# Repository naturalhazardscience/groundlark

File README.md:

# Groundlark — open hardware for seismic and environmental monitoring

Groundlark is a family of hardware boards and companion software for seismic
and environmental monitoring. Each board has its own hardware directory, with
shared component libraries, interfaces and validation tools.

The family has **three products**: the Groundlark FPGA HAT, Skylark and
Burrowlark USB sensor heads. All share the sensor contracts, simulation tools and local workbench.

## Groundlark

**Seismic monitoring on a Raspberry Pi.** The active
[Groundlark FPGA HAT](hw/groundlark-fpga-hat/README.md), model **DAQHAT-01**, is a
140 × 56 mm, six-layer FR-4 board with three XYZ LSM6DSO IMUs and an ADS122C04
input for an external Racotech geophone, plus a fitted SDP32-125PA infrasound sensor and u-blox MAX-M10S GNSS with a side-facing SMA antenna connector. The stack is **Pi → HAT → Trenz
Artix-7 200T FPGA**. Pi acquisition works independently of a configured FPGA.

The [internal FPGA link](docs/fpga-host-link.md) provides six QSPI wires, UART,
reset and switched Pi-driven JTAG. An SPI echo bitstream is implemented;
accelerated sensor processing and native quad transfers remain future work.
The FPGA uses a separate Nexys Video-compatible 12 V, center-positive adapter through J83 and an onboard 3.326 V converter. See the [power limits](docs/trenz-hat.md).

**Status:** active prototype. Physical power, fit, timing, noise and thermal
qualification remain pending. See the [stack assembly guide](docs/stack-assembly.md),
[JLCPCB instructions](docs/jlcpcb-assembly.md) and [bench procedure](docs/bench-procedure.md).
The JLCPCB package targets one assembled HAT; sourcing, placement and J1 fit
checks remain open. Fabrication packages stay local in ignored `hw/releases/`.

*R3 [prototype enclosure](hw/mechanical/daqhat-01-case/README.md), current
140 mm HAT CAD with GNSS/SMA, infrasound, TI Pi supervision and independent FPGA power, vendor Trenz components and a detailed
[Pi 4B model](hw/shared/models/raspberrypi4/README.md) by integrated-circuit / FreeCAD
community (CC BY 3.0). Clear PETG appearance, risers, geophone and wiring are approximate.
Physical fit remains unqualified. [Render provenance](docs/images/groundlark-gnss.json).*

[Closed enclosure render provenance](docs/images/groundlark-gnss-closed.json).
Measured gain/offset workflows and PCB probe access are in the
[calibration guide](docs/calibration.md). Seismic recordings support local
[miniSEED export](docs/miniseed.md).

## Skylark

**Outdoor air-quality monitoring over USB.** [Skylark USB](hw/skylark-usb/README.md)
combines a vertical **90 × 100 mm PCB** with a removable sensor tray and a
**130 × 94 × 185 mm bell enclosure**.

- **Particles:** Plantower PMS5003, with separate downward-facing inlet and exhaust paths.
- **Gases:** socketed SGX-7SO2-AQ-20 sulfur dioxide and SGX-7H2S-AQ-25 hydrogen sulfide cells.
- **Weather:** SHT40 temperature/humidity and BMP390 barometric pressure.
- **Connection:** USB-C power and data through an STM32F072 microcontroller.
- **Housing:** printable bell, rear M4 keyhole mounts and a removable tray with
  separate PMS cradle and splash cover. Bottom ventilation is sheltered by a 25 mm skirt.

[Prototype firmware](sw/skylark/README.md) implements sensor acquisition and
USB streaming. The shared workbench includes Skylark simulation, recording/replay,
board-specific tests and an interactive 3D PCB. Gas data retains separate raw
working and auxiliary electrode counts; concentrations require calibration.

**Status:** Rev A PCB, Rev G enclosure and prototype firmware are implemented.
Physical fit, USB power behavior, analog performance, gas response and weather
resistance still require qualification. The ventilated enclosure has no assigned
IP rating. Follow the [PCB guide](hw/skylark-usb/README.md) and
[enclosure assembly instructions](hw/skylark-usb/mechanical/bell/README.md).

*Render: native PCB artwork and authored component models in the CAD-derived
tray, with the bell set beside it. Component bodies are dimension envelopes;
fasteners and cable dressing are illustrative. [Render provenance](docs/images/skylark-assembly.json).*

## Burrowlark

**Remote magnetic and enclosure-climate sensing over USB.**
[Burrowlark USB](hw/burrowlark-usb/README.md), model **DAQUSB-01**, carries four
RM3100 magnetometers on a 30 mm square grid and an SHT45 temperature/humidity
sensor. One STM32F042K6 coordinates their measurements and sends each sensor's
raw data and timing evidence to the Pi over USB-C.
The SDP32-125PA infrasound sensor is fitted on Groundlark DAQHAT-01.

**Status:** routed prototype hardware, MCU firmware and workbench simulation are
implemented. Physical USB, synchronization, magnetic cross-talk and noise
qualification remain pending. See the
[USB sensor-head guide](docs/usb-sensor-head.md) for interfaces and assembly details.

*Render: native 96 × 70 mm PCB with favicon, Burrowlark name and DAQUSB-01 / REV B1
silkscreen, four RM3100 modules and SHT45 U6/C10; the former infrasound
footprint and bypass capacitor are removed. Module, fuse and SHT45 bodies are simplified
dimensional envelopes. [Render provenance](hw/burrowlark-usb/boards/groundlark-field-head/render-provenance.json).*

## Sensor workbench

The dark-mode Python UI lets you switch between Groundlark, Skylark and
Burrowlark, with interactive 3D views, raw-data charts, stimulus/fault controls,
board-specific tests and recording/replay.
No hardware or Docker is required. Follow the
[beginner walkthrough](docs/sensor-workbench.md) to create your first signal.

```powershell
# Windows: set up once, then launch
./setup-ui.ps1 -Check
./ui.ps1
```

On Linux/macOS, use `sh ./setup-ui.sh --check`, then `sh ./ui.sh`.
Open **http://127.0.0.1:8080**. Tools and dependencies stay in ignored `.local/`.

This is an actual browser screenshot with simulated data. Select the geophone
can or its HAT input to highlight both and inspect the same ADC stream.
Use the **Board** selector for the FPGA HAT, Burrowlark or Skylark.
**Test selected board** runs the selected board’s checks; the HAT test covers all
six sensors over eight simulated seconds. IMU, ADC and GNSS use production Pi
drivers on modeled buses; infrasound uses a raw-response model pending its Pi
driver. Signal checks and recordings/results are downloadable.
The Groundlark GNSS panel also models disconnected or shorted antennas, lock
loss and recovery, and PPS loss independently.
The UI simulates and replays; physical acquisition uses the [Pi software](docs/sensor-software.md).
Live seismic capture stores raw geophone and IMU counts locally as
[miniSEED 3](docs/miniseed.md), with SSREC companions for diagnostics and replay.

## Project files and tests

| Directory | Contents |
| --- | --- |
| [hw/](hw/README.md) | Four product directories, shared component resources, hardware checks and SPICE. |
| [sw/](sw/README.md) | Pi acquisition, contracts, simulator, FPGA and remote firmware interfaces. |
| [docs/](docs/README.md) | Setup, hardware specifications, assembly, interfaces and testing instructions. |
| [environment/](docs/portable-lab.md) | Pinned Docker test environment and bounded cleanup tooling. |

For the full test environment, run `./lab.ps1 build` once, then `./lab.ps1 test`.
Use `./lab.ps1 test -Profile software` for sensor contracts, acquisition,
recording/replay and recovery. Use `./lab.ps1 test -Profile simulation` for fresh
circuit builds, CAD checks and all models while excluding the procurement release
gate. See the [simulation scope](docs/simulation-validation.md) and [portable lab guide](docs/portable-lab.md)
for Linux commands, test scope, five-run retention and cleanup.

Hardware sources: [DAQHAT-01 circuit](hw/groundlark-fpga-hat/elec/hat_trenz.ato),
[KiCad PCB](hw/groundlark-fpga-hat/boards/groundlark-daqhat-01/groundlark-daqhat-01.kicad_pcb),
[Burrowlark DAQUSB-01](hw/burrowlark-usb/boards/groundlark-field-head/groundlark-field-head.kicad_pcb), and
[Skylark USB](hw/skylark-usb/boards/skylark-usb/skylark-usb.kicad_pcb).
See [build instructions](docs/build.md) and [source references](docs/sources.md).

## License

Project-authored code, hardware designs and documentation use the [MIT License](LICENSE).
Third-party assets and dependencies retain their own licenses and attribution.

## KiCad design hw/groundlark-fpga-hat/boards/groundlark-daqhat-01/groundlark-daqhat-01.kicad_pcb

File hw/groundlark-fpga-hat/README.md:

# Groundlark FPGA HAT — DAQHAT-01

Underside TP90–TP93 provide passive calibration probe access; see the [bench calibration guide](../../docs/calibration.md). No additional GPIO or enclosure opening is required.

The active 140 × 56 mm, six-layer Trenz carrier combines three XYZ IMUs and
an ADS122C04 input for an external Racotech geophone, plus a fitted SDP32-125PA
infrasound pressure sensor on I2C1 (0x21), with a 200 Hz averaged acquisition
profile targeting the [1–20 Hz landslide research band](../../docs/sensor-response.md).
The stack is Raspberry Pi,
DAQHAT-01, then Trenz TE0712-03-81I36-A. Physical qualification remains pending.
J90 uses a horizontal Phoenix 1803280 header with the existing 1803581 cable
plug. Pin order remains positive, negative, shield.

MAX-M10S GNSS uses Pi I²C1 and BCM24 PPS, with a side-facing SMA and a
TPS2553 antenna fault limiter. ISO1640 side 2 faces the Pi/GNSS bus. J130 feeds
the separate MSPM0L1106 supervisor and 5.115 V Pi supply; battery policy and
physical qualification remain pending; prototype MCU firmware is implemented.
See [GNSS setup](../../docs/gnss-hardware.md) for the matched RF input and
[external pressure filter](../mechanical/daqhat-01-pressure/README.md) for the
simulation-defined pneumatic accessory; it is outside the PCB package.

J83 takes a Nexys Video-compatible 12 V, center-positive 5.5/2.1 mm adapter
rated at least 3 A. It faces the opposite edge from the geophone. U80 supplies
the FPGA independently of the Pi, with a 3 A output allocation; SW80 turns this
supply off/on. The first 25 mm of the extension contains FPGA input protection and conversion. Check the documented voltage, thermal and enclosure limits before
building; the supply remains an unqualified prototype.

- [Electrical source](elec/hat_trenz.ato)
- [Placement inputs](layout/placement.json)
- [Routed KiCad project](boards/groundlark-daqhat-01/groundlark-daqhat-01.kicad_pro)
- [Native routing snapshot](boards/groundlark-daqhat-01/groundlark-daqhat-01.ses)
- [Hardware and power specifications](../../docs/trenz-hat.md)
- [Pi and external source budgets](../../docs/power-supplies.md)
- [Sensor bandwidth and timing](../../docs/sensor-response.md)
- [Assembly instructions](../../docs/stack-assembly.md)

Build target: `trenz_hat` in [hw/ato.yaml](../ato.yaml). Use the root portable lab
for validation. `simulation/` contains bounded supporting-circuit models;
`mechanical/` retains earlier mechanical artifacts with their recorded status.
FPGA sources remain under [sw/fpga/](../../sw/fpga/README.md).

Assembly uses an 8.5 mm JLCPCB socket, two external GPIO risers and measured
supports (28.06 mm nominal Pi gap). Sensor supply and bias returns have local
ground stitches. Only the two RF inductor stock observations were refreshed on 2026-10-20; see [JLCPCB assembly](../../docs/jlcpcb-assembly.md).

D90 uses TI **TPD2E2U06QDCKRQ1 / JLCPCB C915089** as the pin-compatible
replacement for TPD2E2U06DCKR. Its SC-70 footprint and routing are unchanged.
The 190 fitted placements have 72 exact-MPN BOM lines, all with catalog
mappings. L140/L141 use Murata LQW15AN56NG80D / C1330587 and
LQW15AN3N6G80D / C412276 as documented assembly substitutions. The RF model
uses these selected parts; the sensor-acquisition/UI simulator is unchanged.
U23 uses the redesigned SDP32-125PA circuit and driver. All 190 placements now
have frozen supplier-pad registrations, including bottom-side projections,
switch mounting lands and the SMA body direction. D140 uses the manufacturer's
SOD882 land and paste dimensions. See the assembly guide before ordering.

The revised signal routing passes the expanded adjacent-layer coupling model: all
217 evaluated pairs meet the 0.20 V allocation; worst excursion is 0.188 V.
The full build enforces the supplier-placement release gate.
L141 is a provisional 3.6 nH VNA tuning position; D130 junction-temperature
qualification remains open. See [simulation scope](../../docs/simulation-validation.md).

Use the [R3 enclosure](../mechanical/daqhat-01-case/README.md) for the 140 × 56 mm
board. It adds power-wing supports, a rear DC opening opposite the geophone and
switch access. First-print fit and thermal qualification remain pending.

## Pi power supervisor

J130 accepts **8–18 V DC** from an externally protected battery/controller.
U130 is TI MSPM0L1106TRHBR; U131 powers it continuously while U132/U133 supply
and disconnect the Pi through header pins 2/4. The combined Pi/HAT allocation
is 3 A at nominal 5.115 V, for the Pi 4 stack. Do not simultaneously power the
Pi through USB-C. Keep J83's separate 12 V FPGA input independent.

Battery thresholds and delays are configurable placeholders, shipped disabled
in [power-policy.example.json](../../sw/pi/deploy/power-policy.example.json).
Prototype MCU firmware is implemented; physical power qualification remains pending. An
unprogrammed MCU leaves the Pi off; fitting the JP130 shunt provides manual
bench operation. Remove it before automatic supervision. See the
[operating specification](../../docs/power-supplies.md#pi-supervisor-and-battery-input).

## GNSS timing

U21 is a MAX-M10S-00B on Pi I2C1 (0x42); BCM24/header 18 captures PPS.
J140 is a side-facing SMA for a 3.3 V active antenna drawing at most 20 mA.
The 140 x 56 mm outline and independent FPGA power remain unchanged. Use the
updated R3 enclosure with its +X antenna access slot. See [antenna setup](../../docs/gnss-hardware.md)
and [timing capture/correlation](../../docs/utc-timing.md). Browser tests cover
modeled lock/PPS loss and recording/replay; physical millisecond alignment remains unqualified.

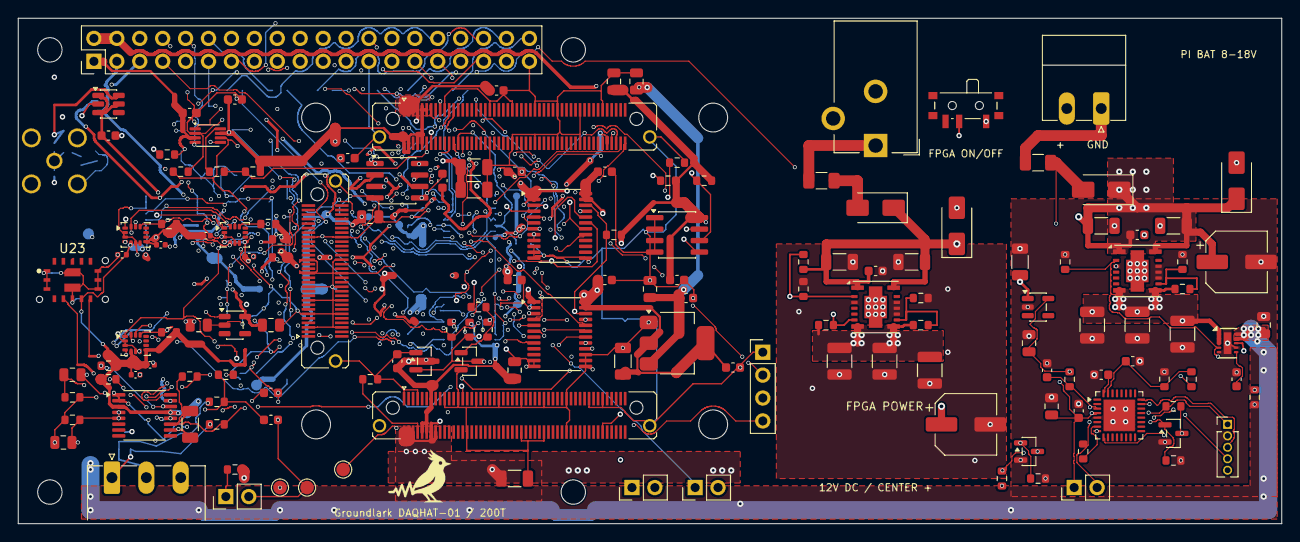
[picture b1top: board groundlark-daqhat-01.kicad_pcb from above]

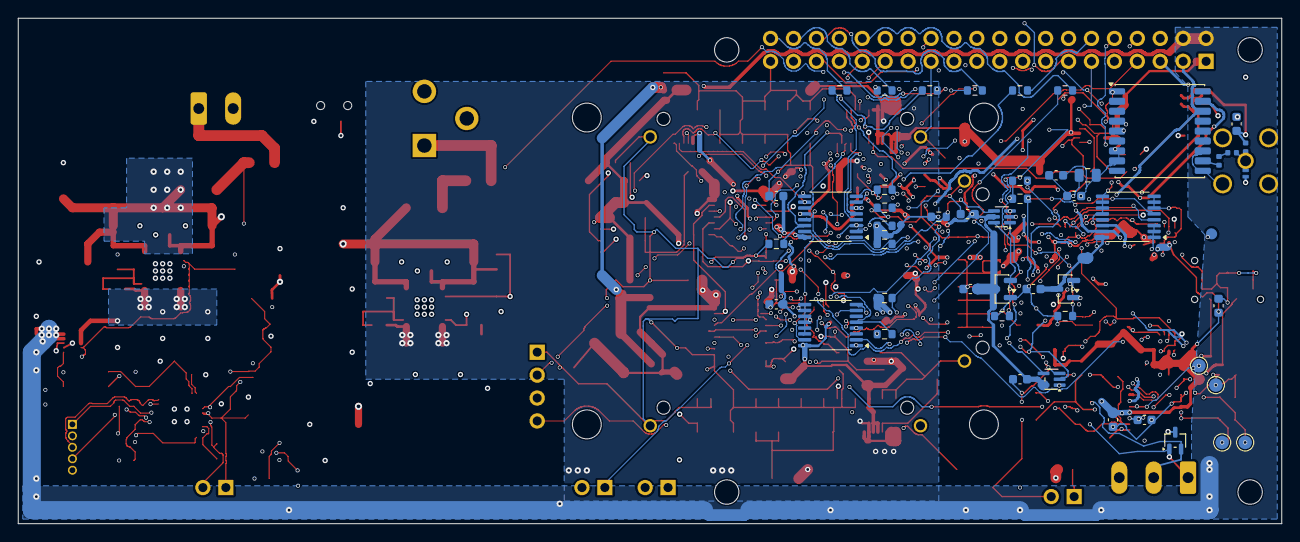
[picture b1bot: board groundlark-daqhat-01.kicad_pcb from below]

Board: 6 copper layers, 140.0 x 56.0 mm, 205 parts (48 on the bottom side), 110 nets.

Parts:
C1, C24, C41, C43, C44, C45, C46, C47, C48, C49, C75, C76, C77, C83, C95, C96, C100, C101, C102, C103, C104, C105, C106, C147, C152: 100n; Capacitor_SMD__C_0603_1608Metric
C2, C3, C40, C93, C94: 10u; Capacitor_SMD__C_0805_2012Metric
C12, C13, C14, C15, C16, C17: 100n; Capacitor_SMD__C_0402_1005Metric
C42, C80, C81, C82: 22u; Capacitor_SMD__C_1206_3216Metric
C84, C85, C146, C149, C150: 4.7u; Capacitor_SMD__C_0805_2012Metric
C86, C87, C131, C132, C133: 10u; PWR_C_1206_3216Metric
C88, C134, C141: 100n; PWR_C_0603_1608Metric
C89, C135: 47u; PWR_CP_Elec_6.3x7.7
C90: 100n C0G; Capacitor_SMD__C_1206_3216Metric
C91, C92: 1n C0G; Capacitor_SMD__C_0603_1608Metric
C110, C111, C112, C136, C137, C138: 22u; PWR_C_1210_3225Metric
C130: 4.7u; SUP_C_0805_2012Metric
C139, C144, C145, C151: 10n; SUP_C_0603_1608Metric
C140, C142: 10u; SUP_C_0805_2012Metric
C143: 470n; SUP_C_0603_1608Metric
C148: 47p C0G; GNSS_C0402
D80, D130: B340A; PWR_D_SMA
D81: SMAJ15A; PWR_D_SMA
D90: TPD2E2U06; Package_TO_SOT_SMD__SOT-323_SC-70
D131: SMAJ18A; SUP_D_SMA
D140: PESD5V0F1BL; GNSS_SOD882
F80: 0466002.NRHF; PWR_Fuse_1206_3216Metric
F130: 4A fuse; SUP_Fuse_1206_3216Metric
H1, H2, H3, H4: M2.5 NPTH; MountingHole__MountingHole_2.7mm_M2.5
H80, H81, H82, H83: M3 / 8 mm spacer; TZ_TZ_HOLE
J1: Raspberry Pi 40-pin; Connector_PinHeader_2.54mm__PinHeader_2x20_P2.54mm_Vertical
J4: FPGA test UART/reset; Connector_PinHeader_2.54mm__PinHeader_1x04_P2.54mm_Vertical
J80, J81: LSHM-150-04.0-L-DV-A-S-K-TR; TZ_TZ100
J82: LSHM-130-04.0-L-DV-A-S-K-TR; TZ_TZ60
J83: 12V DC / CENTER +; PWR_BarrelJack_CUI_PJ-102AH_Horizontal
J90: GEO + / - / SHIELD; Connector_Phoenix_MC__PhoenixContact_MC_1,5_3-G-3.81_1x03_P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
J130: PI BATTERY 8-18V; SUP_PhoenixContact_MC_1,5_2-G-3.81_1x02_P3.81mm_Horizontal
J131: SWD / 3V3 REF; SUP_PinHeader_1x05_P1.27mm_Vertical
J140: GNSS ANT / 3V3; GNSS_HL_SMA_KWE_02
JP1: EEPROM write enable; Connector_PinHeader_2.54mm__PinHeader_1x02_P2.54mm_Vertical
JP80, JP81: TSW-102-07-G-S; TZ_TZ_JP
JP130: BENCH RUN; SUP_PinHeader_1x02_P2.54mm_Vertical
L140: 56n; GNSS_HP0402
L141: 3.6n; GNSS_HP0402
Q1: 2N7002; Package_TO_SOT_SMD__SOT-23
Q130, Q131: 2N7002; SUP_SOT-23
R1, R2: 3.9k; Resistor_SMD__R_0603_1608Metric
R3, R65, R90, R91: 1k; Resistor_SMD__R_0603_1608Metric
R11, R12, R13, R50, R63, R64, R80, R81, R94, R95, R97, R106, R107, R108, R109, R110, R111, R113, R115, R118: 10k; Resistor_SMD__R_0603_1608Metric
R51, R62, R66, R112, R114, R116, R117: 100k; Resistor_SMD__R_0603_1608Metric
R52, R53: 4.7k; Resistor_SMD__R_0603_1608Metric
R61: 47; Resistor_SMD__R_0603_1608Metric
R92, R93: 1M; Resistor_SMD__R_0603_1608Metric
R96, R100, R101, R102, R103, R104, R105: 22; Resistor_SMD__R_0603_1608Metric
R120, R124, R130, R138, R141: 10k; PWR_R_0603_1608Metric
R121: 4.30k; PWR_R_0603_1608Metric
R122, R132, R137, R139, R140: 100k; PWR_R_0603_1608Metric
R123: 15k; PWR_R_0603_1608Metric
R131: 2.43k; SUP_R_0603_1608Metric
R133: 2k; SUP_R_0603_1608Metric
R134: 47k; SUP_R_0603_1608Metric
R135: 1M; SUP_R_0603_1608Metric
R136: 150k; SUP_R_0603_1608Metric
SW80: FPGA OFF / ON; PWR_SW_SPDT_PCM12
TP1: SENS_3V3; TestPoint__TestPoint_Pad_D1.5mm
TP2, TP90: GND; TestPoint__TestPoint_Pad_D1.5mm
TP4: SENSOR_OE_N; TestPoint__TestPoint_Pad_D1.5mm
TP91: GEO_VCM; TestPoint__TestPoint_Pad_D1.5mm
TP92: GEO_AVDD; TestPoint__TestPoint_Pad_D1.5mm
TP93: GEO_DRDY_N; TestPoint__TestPoint_Pad_D1.5mm
U1: 24LC32A; Package_SO__SOIC-8_3.9x4.9mm_P1.27mm
U11, U12, U13: LSM6DSOTR; Package_LGA__LGA-14_3x2.5mm_P0.5mm_LayoutBorder3x4y
U21: MAX-M10S-00B; RF_GPS__ublox_MAX
U22: ADS122C04; Package_SO__TSSOP-16_4.4x5mm_P0.65mm
U23: SDP32-125PA; Groundlark__SDP32
U40: TLV1117LV33DCYR; Package_TO_SOT_SMD__SOT-223-3_TabPin2
U41, U42: SN74LVC8T245PWR; Package_SO__TSSOP-24_4.4x7.8mm_P0.65mm
U43: ISO1640BDR; Package_SO__SOIC-8_3.9x4.9mm_P1.27mm
U51: TXU0202DCUR; Package_SO__VSSOP-8_2.3x2mm_P0.5mm
U52: TLV803EA30DBZR; Package_TO_SOT_SMD__SOT-23
U80, U132: TPSM53603; PWR_Texas_B3QFN-14-1EP_5x5.5mm_P0.65mm
U100, U101: TMUX1574PWR; Package_SO__TSSOP-16_4.4x5mm_P0.65mm
U102: TCA9534PWR; Package_SO__TSSOP-16_4.4x5mm_P0.65mm
U103: SN74LVC1G10DCKR; Package_TO_SOT_SMD__SOT-363_SC-70-6
U104, U105: TLV809EA30DBZR; Package_TO_SOT_SMD__SOT-23
U106: SN74LVC1G08DCKR; Package_TO_SOT_SMD__SOT-353_SC-70-5
U130: MSPM0L1106; SUP_QFN-32-1EP_5x5mm_P0.5mm_EP3.45x3.45mm
U131, U140: TPS70933; SUP_SOT-23-5
U133: TPS22953; SUP_Texas_WSON10_DQC0010A
U141: TPS2553; GNSS_SOT23_6

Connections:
BAT_FUSED: D130.2, F130.2, R135.1
BAT_INPUT: F130.1, J130.1
BAT_PROTECTED: C131.1, C132.1, C133.1, C134.1, C135.1, D130.1, D131.1, U131.1, U132.1, U132.14
BUCK_EN: R122.2, R123.1, SW80.2, U80.2
BUCK_FB: R120.2, R121.1, U80.9
EEP_WP: JP1.1, R3.1, U1.7
EXT_12V: F80.1, J83.1
FPGA_3V3: C76.1, C77.1, C84.1, C85.1, C100.1, C101.1, C103.1, C105.1, C106.1, J80.10, J80.12, J80.13, J81.2, J81.4, J81.8, J81.9, J81.10, J81.11, J81.92, R63.2, R64.2, R108.2, R111.2, R113.2, R115.2, U51.7, U52.3, U100.16, U101.16, U103.5, U105.3, U106.5
FPGA_CONFIG_RESET_N: J81.17, JP81.1
FPGA_EN1: J80.27, JP80.1, R124.2, U80.6
FPGA_IO_ENABLE: J1.22, R62.1, U51.6, U106.2
FPGA_JTAGEN: J80.90, R80.1
FPGA_LINK_CS_N: J81.23, R111.1, U101.2
FPGA_LINK_DQ0: J81.22, U100.5
FPGA_LINK_DQ1: J81.24, U100.11
FPGA_LINK_DQ2: J81.26, R116.1, U100.14
FPGA_LINK_DQ3: J81.28, R117.1, U101.5
FPGA_LINK_SCLK: J81.21, R112.1, U100.2
FPGA_NOSEQ: J80.8, R81.1
FPGA_RESET_GATE: Q1.1, R65.2, R66.1
FPGA_RESET_GPIO: J1.11, R65.1
FPGA_RESET_N: J4.4, J81.13, Q1.3, R64.1, U52.2
FPGA_UART_DRIVE: R61.1, U51.8
FPGA_UART_RX: J4.2, J81.12, R61.2, R63.1
FPGA_UART_TX: J4.3, J81.14, U51.1
FPGA_VIN: C80.1, C81.1, C82.1, C83.1, C110.1, C111.1, C112.1, J80.2, J80.4, J80.6, J80.14, J80.16, J81.1, J81.3, J81.5, J81.7, R120.1, R124.1, U80.7, U80.8
FUSED_12V: D80.2, F80.2
GEO_AIN_N: C90.2, C92.1, R91.2, R93.1, U22.10
GEO_AIN_P: C90.1, C91.1, R90.2, R92.1, U22.11
GEO_AVDD: C94.1, C95.1, R94.1, R96.2, TP92.1, U22.12
GEO_DRDY_N: R97.1, TP93.1, U22.14, U42.16
GEO_N: D90.2, J90.2, R91.1
GEO_P: D90.1, J90.1, R90.1
GEO_VCM: C93.1, R92.2, R93.2, R94.2, R95.1, TP91.1
GND: C1.2, C2.2, C3.2, C12.2, C13.2, C14.2, C15.2, C16.2, C17.2, C24.2, C40.2, C41.2, C42.2, C43.2, C44.2, C45.2, C46.2, C47.2, C48.2, C49.2, C75.2, C76.2, C77.2, C80.2, C81.2, C82.2, C83.2, C84.2, C85.2, C86.2, C87.2, C88.2, C89.2, C91.2, C92.2, C93.2, C94.2, C95.2, C96.2, C100.2, C101.2, C102.2, C103.2, C104.2, C105.2, C106.2, C110.2, C111.2, C112.2, C130.2, C131.2, C132.2, C133.2, C134.2, C135.2, C136.2, C137.2, C138.2, C139.2, C140.2, C141.2, C142.2, C143.2, C144.2, C145.2, C146.2, C147.2, C149.2, C150.2, C151.2, C152.2, D81.2, D90.3, D131.2, D140.2, J1.6, J1.9, J1.14, J1.20, J1.25, J1.30, J1.34, J1.39, J4.1, J80.1, J80.7, J80.19, J80.25, J80.30, J80.33, J80.43, J80.53, J80.54, J80.63, J80.64, J80.73, J80.74, J80.83, J80.89, J80.101, J81.19, J81.39, J81.40, J81.49, J81.50, J81.59, J81.60, J81.69, J81.70, J81.79, J81.80, J81.89, J81.101, J82.5, J82.6, J82.11, J82.12, J82.17, J82.18, J82.23, J82.24, J82.29, J82.30, J82.35, J82.36, J82.45, J82.46, J82.61, J83.2, J90.3, J130.2, J131.2, J140.2, JP1.2, JP80.2, JP81.2, Q1.2, Q130.2, Q131.2, R51.2, R62.2, R66.2, R80.2, R81.2, R95.2, R106.2, R107.2, R109.2, R110.2, R112.2, R114.2, R116.2, R117.2, R121.2, R123.2, R131.2, R132.2, R133.2, R136.2, R137.2, R139.2, SW80.1, TP2.1, TP90.1, U1.1, U1.2, U1.3, U1.4, U11.2, U11.3, U11.6, U11.7, U12.2, U12.3, U12.6, U12.7, U13.2, U13.3, U13.6, U13.7, U21.1, U21.5, U21.10, U21.12, U22.1, U22.2, U22.4, U22.5, U23.1, U23.2, U23.3, U23.6, U23.9, U23.10, U23.11, U23.17, U40.1, U41.8, U41.9, U41.10, U41.11, U41.12, U41.13, U42.2, U42.11, U42.12, U42.13, U42.14, U42.15, U42.17, U43.4, U43.5, U51.2, U52.1, U80.3, U80.10, U80.11, U80.12, U80.15, U100.8, U101.8, U101.9, U101.10, U101.11, U101.12, U101.13, U101.14, U102.1, U102.2, U102.3, U102.6, U102.7, U102.8, U102.9, U102.10, U102.11, U102.12, U103.2, U104.1, U105.1, U106.3, U130.5, U130.33, U131.2, U132.3, U132.10, U132.11, U132.12, U132.15, U133.5, U133.7, U133.11, U140.2, U141.2
GNSS_ANT: C148.1, D140.1, J140.1, L140.2
GNSS_BIAS: C151.1, L140.1, U141.6
GNSS_LDO: C150.1, C152.1, U140.5, U141.1, U141.3, U141.5
GNSS_MATCH: C148.2, L141.1
GNSS_PPS: J1.18, U21.4
GNSS_RF: L141.2, U21.11
I2C_SCL: R53.1, U22.16, U23.5, U43.3
I2C_SDA: R52.1, U22.15, U23.8, U43.2
ID_SCL: J1.28, R2.1, U1.6
ID_SDA: J1.27, R1.1, U1.5
IMU1_CS: R11.1, U11.12, U41.19
IMU1_INT: U11.4, U42.20
IMU2_CS: R12.1, U12.12, U41.18
IMU2_INT: U12.4, U42.19
IMU3_CS: R13.1, U13.12, U41.17
IMU3_INT: U13.4, U42.18
JTAG_TCK: J81.100, R114.1, U100.3
JTAG_TDI: J81.96, R115.1, U100.6
JTAG_TDO: J81.98, U100.10
JTAG_TMS: J81.94, R113.1, U100.13
LINK_ARMED_REQUEST: U103.1, U106.4
LINK_CS_N: R104.2, U101.4
LINK_DQ0: R101.2, U100.7
LINK_DQ1: R102.2, U100.9
LINK_DQ2: R103.2, U100.12
LINK_DQ3: R105.2, U101.7
LINK_FPGA_GOOD: R110.1, U103.6, U105.2
LINK_JTAG_SEL: R106.1, U100.1, U101.1, U102.4
LINK_OE_N: R108.1, U100.15, U101.15, U103.4
LINK_PI_GOOD: R109.1, U103.3, U104.2
LINK_REQUEST: R107.1, U102.5, U106.1
LINK_SCLK: R100.2, U100.4
PI_3V3: C1.1, C2.1, C44.1, C46.1, C49.1, C75.1, C102.1, C104.1, C146.1, C147.1, J1.1, J1.17, R1.2, R2.2, R3.2, R50.2, R118.2, R138.1, U1.8, U21.7, U21.8, U41.1, U41.2, U42.1, U43.8, U51.3, U102.16, U104.3
PI_5V: C3.1, C40.1, C41.1, C140.1, C149.1, J1.2, J1.4, R133.1, U40.3, U133.9, U133.10, U140.1
PI_BUCK_FB: R130.2, R131.1, U132.9
PI_GEO_DRDY_N: J1.7, U42.8
PI_HALTED: J1.33, Q131.1, R139.1
PI_I2C_SCL: J1.5, U21.17, U43.6, U102.14
PI_I2C_SDA: J1.3, U21.16, U43.7, U102.15
PI_IMU1_CS: J1.24, U41.5
PI_IMU1_INT: J1.13, U42.4
PI_IMU2_CS: J1.26, U41.6
PI_IMU2_INT: J1.15, U42.5
PI_IMU3_CS: J1.29, U41.7
PI_IMU3_INT: J1.16, U42.6
PI_LINK_CS_N: J1.12, R104.1
PI_LINK_DQ0: J1.38, R101.1
PI_LINK_DQ1: J1.35, R102.1
PI_LINK_DQ2: J1.36, R103.1
PI_LINK_DQ3: J1.32, R105.1
PI_LINK_SCLK: J1.40, R100.1
PI_RAW_5V: C136.1, C137.1, C138.1, R130.1, U132.7, U132.8, U133.1, U133.2, U133.3, U133.8
PI_SHUTDOWN_N: J1.31, Q130.3, R138.2
PI_SPI_MISO: J1.21, U42.3
PI_SPI_MOSI: J1.19, U41.3
PI_SPI_SCLK: J1.23, U41.4
PI_SWITCH_CT: C139.1, U133.6
PI_UART_RX: J1.10, R118.1, U51.4
PI_UART_TX: J1.8, U51.5
PROTECTED_12V: C86.1, C87.1, C88.1, C89.1, D80.1, D81.1, R122.1, U80.1, U80.14
SENSOR_OE_N: J1.37, R50.1, TP4.1, U41.22, U42.22
SENS_3V3: C12.1, C13.1, C14.1, C15.1, C16.1, C17.1, C24.1, C42.1, C43.1, C45.1, C47.1, C48.1, C96.1, R11.2, R12.2, R13.2, R52.2, R53.2, R96.1, R97.2, TP1.1, U11.5, U11.8, U12.5, U12.8, U13.5, U13.8, U22.3, U22.13, U23.7, U40.2, U41.23, U41.24, U42.23, U42.24, U43.1
SPI_MISO: R51.1, U11.1, U12.1, U13.1, U42.21
SPI_MOSI: U11.14, U12.14, U13.14, U41.21
SPI_SCLK: U11.13, U12.13, U13.13, U41.20
SUP_3V3: C130.1, C141.1, C142.1, J131.1, JP130.1, R134.2, R140.1, U130.4, U131.5
SUP_ACK_N: Q131.3, R140.2, U130.9
SUP_BAT_ADC: C145.1, R135.2, R136.1, U130.31
SUP_CORE: C143.1, U130.32
SUP_NRST: C144.1, J131.5, R134.1, U130.3
SUP_REQUEST: Q130.1, R137.1, U130.8
SUP_RUN: JP130.2, R132.1, R141.2, U132.2, U133.4
SUP_RUN_DRIVE: R141.1, U130.7
SUP_SWCLK: J131.3, U130.24
SUP_SWDIO: J131.4, U130.23

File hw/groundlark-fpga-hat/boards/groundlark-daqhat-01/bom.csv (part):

Reference,Value,MPN,Footprint,DNP,Note
J1,Raspberry Pi 40-pin,Samtec ESQ-120-23-G-D,Connector_PinHeader_2.54mm__PinHeader_2x20_P2.54mm_Vertical,False,"Header land pattern matches bottom mounted socket top-view numbering; tall stack, check Pi 4/5 cooler clearance."
U1,24LC32A,24LC32A-I/SN,Package_SO__SOIC-8_3.9x4.9mm_P1.27mm,False,
R1,3.9k,RC0603FR-073K9L,Resistor_SMD__R_0603_1608Metric,False,
R2,3.9k,RC0603FR-073K9L,Resistor_SMD__R_0603_1608Metric,False,
R3,1k,RC0603FR-071KL,Resistor_SMD__R_0603_1608Metric,False,
JP1,EEPROM write enable,EEPROM write enable,Connector_PinHeader_2.54mm__PinHeader_1x02_P2.54mm_Vertical,False,Fit shunt only while programming ID EEPROM.
C1,100n,GRM188R71H104KA93D,Capacitor_SMD__C_0603_1608Metric,False,
C2,10u,GRM21BR61A106KE19L,Capacitor_SMD__C_0805_2012Metric,False,
C3,10u,GRM21BR61A106KE19L,Capacitor_SMD__C_0805_2012Metric,False,
U11,LSM6DSOTR,LSM6DSOTR,Package_LGA__LGA-14_3x2.5mm_P0.5mm_LayoutBorder3x4y,False,
C12,100n,GRM155R71C104KA88D,Capacitor_SMD__C_0402_1005Metric,False,
C13,100n,GRM155R71C104KA88D,Capacitor_SMD__C_0402_1005Metric,False,
R11,10k,RC0603FR-0710KL,Resistor_SMD__R_0603_1608Metric,False,
U12,LSM6DSOTR,LSM6DSOTR,Package_LGA__LGA-14_3x2.5mm_P0.5mm_LayoutBorder3x4y,False,
C14,100n,GRM155R71C104KA88D,Capacitor_SMD__C_0402_1005Metric,False,
C15,100n,GRM155R71C104KA88D,Capacitor_SMD__C_0402_1005Metric,False,
R12,10k,RC0603FR-0710KL,Resistor_SMD__R_0603_1608Metric,False,
U13,LSM6DSOTR,LSM6DSOTR,Package_LGA__LGA-14_3x2.5mm_P0.5mm_LayoutBorder3x4y,False,
C16,100n,GRM155R71C104KA88D,Capacitor_SMD__C_0402_1005Metric,False,
C17,100n,GRM155R71C104KA88D,Capacitor_SMD__C_0402_1005Metric,False,
R13,10k,RC0603FR-0710KL,Resistor_SMD__R_0603_1608Metric,False,
J4,FPGA test UART/reset,FPGA UART service ONLY,Connector_PinHeader_2.54mm__PinHeader_1x04_P2.54mm_Vertical,False,Test points for assembled module UART and active-low reset; do not connect a second driving host.
H1,M2.5 NPTH,M2.5 NPTH,MountingHole__MountingHole_2.7mm_M2.5,False,Nonmagnetic standoffs.
H2,M2.5 NPTH,M2.5 NPTH,MountingHole__MountingHole_2.7mm_M2.5,False,Nonmagnetic standoffs.
H3,M2.5 NPTH,M2.5 NPTH,MountingHole__MountingHole_2.7mm_M2.5,False,Nonmagnetic standoffs.
H4,M2.5 NPTH,M2.5 NPTH,MountingHole__MountingHole_2.7mm_M2.5,False,Nonmagnetic standoffs.
U40,TLV1117LV33DCYR,TLV1117LV33DCYR,Package_TO_SOT_SMD__SOT-223-3_TabPin2,False,
C40,10u,GRM21BR61A106KE19L,Capacitor_SMD__C_0805_2012Metric,False,
C41,100n,GRM188R71H104KA93D,Capacitor_SMD__C_0603_1608Metric,False,
C42,22u,GRM31CR61A226KE19L,Capacitor_SMD__C_1206_3216Metric,False,
C43,100n,GRM188R71H104KA93D,Capacitor_SMD__C_0603_1608Metric,False,
U41,SN74LVC8T245PWR,SN74LVC8T245PWR,Package_SO__TSSOP-24_4.4x7.8mm_P0.65mm,False,
U42,SN74LVC8T245PWR,SN74LVC8T245PWR,Package_SO__TSSOP-24_4.4x7.8mm_P0.65mm,False,
C44,100n,GRM188R71H104KA93D,Capacitor_SMD__C_0603_1608Metric,False,
C45,100n,GRM188R71H104KA93D,Capacitor_SMD__C_0603_1608Metric,False,
C46,100n,GRM188R71H104KA93D,Capacitor_SMD__C_0603_1608Metric,False,
C47,100n,GRM188R71H104KA93D,Capacitor_SMD__C_0603_1608Metric,False,
R50,10k,RC0603FR-0710KL,Resistor_SMD__R_0603_1608Metric,False,
R51,100k,RC0603FR-07100KL,Resistor_SMD__R_0603_1608Metric,False,
U43,ISO1640BDR,ISO1640BDR,Package_SO__SOIC-8_3.9x4.9mm_P1.27mm,False,Power-domain isolation only: grounds are joined. Side-1 VOL max 0.71V requires host VIL >=0.8V; verify Pi revision.
C48,100n,GRM188R71H104KA93D,Capacitor_SMD__C_0603_1608Metric,False,
C49,100n,GRM188R71H104KA93D,Capacitor_SMD__C_0603_1608Metric,False,
R52,4.7k,RC0603FR-074K7L,Resistor_SMD__R_0603_1608Metric,False,
R53,4.7k,RC0603FR-074K7L,Resistor_SMD__R_0603_1608Metric,False,
TP1,SENS_3V3,SENS_3V3,TestPoint__TestPoint_Pad_D1.5mm,False,
TP2,GND,GND,TestPoint__TestPoint_Pad_D1.5mm,False,
TP4,SENSOR_OE_N,SENSOR_OE_N,TestPoint__TestPoint_Pad_D1.5mm,False,
U51,TXU0202DCUR,TXU0202DCUR,Package_SO__VSSOP-8_2.3x2mm_P0.5mm,False,
C75,100n,GRM188R71H104KA93D,Capacitor_SMD__C_0603_1608Metric,False,
C76,100n,GRM188R71H104KA93D,Capacitor_SMD__C_0603_1608Metric,False,
R61,47,RC0603FR-0747RL,Resistor_SMD__R_0603_1608Metric,False,
R62,100k,RC0603FR-07100KL,Resistor_SMD__R_0603_1608Metric,False,
R63,10k,RC0603FR-0710KL,Resistor_SMD__R_0603_1608Metric,False,
U52,TLV803EA30DBZR,TLV803EA30DBZR,Package_TO_SOT_SMD__SOT-23,False,"3.0V falling threshold, 200ms nominal release delay; open-drain output."
C77,100n,GRM188R71H104KA93D,Capacitor_SMD__C_0603_1608Metric,False,
R64,10k,RC0603FR-0710KL,Resistor_SMD__R_0603_1608Metric,False,
Q1,2N7002,2N7002,Package_TO_SOT_SMD__SOT-23,False,Pi GPIO17 HIGH asserts chip reset; does not drive a live voltage into unpowered chip.
R65,1k,RC0603FR-071KL,Resistor_SMD__R_0603_1608Metric,False,
R66,100k,RC0603FR-07100KL,Resistor_SMD__R_0603_1608Metric,False,
J80,LSHM-150-04.0-L-DV-A-S-K-TR,LSHM-150-04.0-L-DV-A-S-K-TR,TZ_TZ100,False,Mates JM1; opposite parity; 8 mm board surface gap
J81,LSHM-150-04.0-L-DV-A-S-K-TR,LSHM-150-04.0-L-DV-A-S-K-TR,TZ_TZ100,False,Mates JM2; opposite parity; 8 mm board surface gap
J82,LSHM-130-04.0-L-DV-A-S-K-TR,LSHM-130-04.0-L-DV-A-S-K-TR,TZ_TZ60,False,Mates JM3; opposite parity; 8 mm board surface gap
JP80,TSW-102-07-G-S,TSW-102-07-G-S,TZ_TZ_JP,False,Fit shunt to DISABLE module; open enables on-board sequence
JP81,TSW-102-07-G-S,TSW-102-07-G-S,TZ_TZ_JP,False,Fit shunt to request module configuration reset
R80,10k,RC0603FR-0710KL,Resistor_SMD__R_0603_1608Metric,False,FPGA JTAG selection / spare CPLD control idle pull-down
R81,10k,RC0603FR-0710KL,Resistor_SMD__R_0603_1608Metric,False,FPGA JTAG selection / spare CPLD control idle pull-down
C80,22u,GRM31CR61A226KE19L,Capacitor_SMD__C_1206_3216Metric,False,Carrier local decoupling; module contains core decoupling
C81,22u,GRM31CR61A226KE19L,Capacitor_SMD__C_1206_3216Metric,False,Carrier local decoupling; module contains core decoupling
C82,22u,GRM31CR61A226KE19L,Capacitor_SMD__C_1206_3216Metric,False,Carrier local decoupling; module contains core decoupling
C83,100n,GRM188R71H104KA93D,Capacitor_SMD__C_0603_1608Metric,False,Carrier local decoupling; module contains core decoupling
C84,4.7u,GRM21BR71A475KA73L,Capacitor_SMD__C_0805_2012Metric,False,Carrier local decoupling; module contains core decoupling
C85,4.7u,GRM21BR71A475KA73L,Capacitor_SMD__C_0805_2012Metric,False,Carrier local decoupling; module contains core decoupling
H80,M3 / 8 mm spacer,M3 / 8 mm spacer,TZ_TZ_HOLE,False,
H81,M3 / 8 mm spacer,M3 / 8 mm spacer,TZ_TZ_HOLE,False,
H82,M3 / 8 mm spacer,M3 / 8 mm spacer,TZ_TZ_HOLE,False,
H83,M3 / 8 mm spacer,M3 / 8 mm spacer,TZ_TZ_HOLE,False,
U22,ADS122C04,ADS122C04IPWR,Package_SO__TSSOP-16_4.4x5mm_P0.65mm,False,"I2C 0x40; internal 2.048V reference, gain 64, normal 330 SPS; unused analog/reference inputs open per TI."
J90,GEO + / - / SHIELD,1803280,"Connector_Phoenix_MC__PhoenixContact_MC_1,5_3-G-3.81_1x03_P3.81mm_Horizontal",False,"Horizontal outward entry (+Y). 1 positive, 2 negative, 3 cable shield. Mate Phoenix 1803581. Never connect power."
D90,TPD2E2U06,TPD2E2U06QDCKRQ1,Package_TO_SOT_SMD__SOT-323_SC-70,False,Connector ESD suppression only; not lightning protection.
R90,1k,RC0603FR-071KL,Resistor_SMD__R_0603_1608Metric,False,Matched series input filter / current limiting.
R91,1k,RC0603FR-071KL,Resistor_SMD__R_0603_1608Metric,False,
C90,100n C0G,C3216C0G1H104J160AA,Capacitor_SMD__C_1206_3216Metric,False,C0G differential filter; no piezoelectric X7R on signal path.
C91,1n C0G,C0603C102J5GACTU,Capacitor_SMD__C_0603_1608Metric,False,
C92,1n C0G,C0603C102J5GACTU,Capacitor_SMD__C_0603_1608Metric,False,
R92,1M,RC0603FR-071ML,Resistor_SMD__R_0603_1608Metric,False,
R93,1M,RC0603FR-071ML,Resistor_SMD__R_0603_1608Metric,False,
R94,10k,RC0603FR-0710KL,Resistor_SMD__R_0603_1608Metric,False,
R95,10k,RC0603FR-0710KL,Resistor_SMD__R_0603_1608Metric,False,
C93,10u,GRM21BR61A106KE19L,Capacitor_SMD__C_0805_2012Metric,False,Filtered mid-supply; sensor has no excitation current source.
R96,22,RC0603FR-0722RL,Resistor_SMD__R_0603_1608Metric,False,
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
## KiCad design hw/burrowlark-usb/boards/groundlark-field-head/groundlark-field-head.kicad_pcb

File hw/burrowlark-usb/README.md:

# Burrowlark USB — DAQUSB-01

Burrowlark is the separate 96 × 70 mm USB-C magnetometer and enclosure-climate
sensor head. It uses four identically oriented PNI 14190 RM3100 XYZ modules on a 30 mm square grid; U3/C5 and their pressure-sensor
branches are removed. The DLVR pressure sensor is on DAQHAT-01. Prototype
[USB-head firmware](../../sw/field-head/README.md) has native and ARM checks;
physical qualification remains pending.

Native PCB render with the Groundlark favicon, Burrowlark name and
`DAQUSB-01 / REV B1` front silkscreen. Shared SPI commands start all four conversions together; separate SO and DRDY lines preserve each raw result and completion observation. Internal sensor clocks remain independent.
Module, fuse and SHT45 bodies are simplified envelopes; see
[render provenance](boards/groundlark-field-head/render-provenance.json).

- [Electrical source](elec/field_head.ato)
- [Placement inputs](layout/placement.json)
- [Routed KiCad project](boards/groundlark-field-head/groundlark-field-head.kicad_pro)
- [Assembly and interface guide](../../docs/usb-sensor-head.md)
- [Firmware directory](../../sw/field-head/)

Build target: `field_head` in [hw/ato.yaml](../ato.yaml). Existing CAD filenames
and the DAQUSB-01 model identifier are preserved.

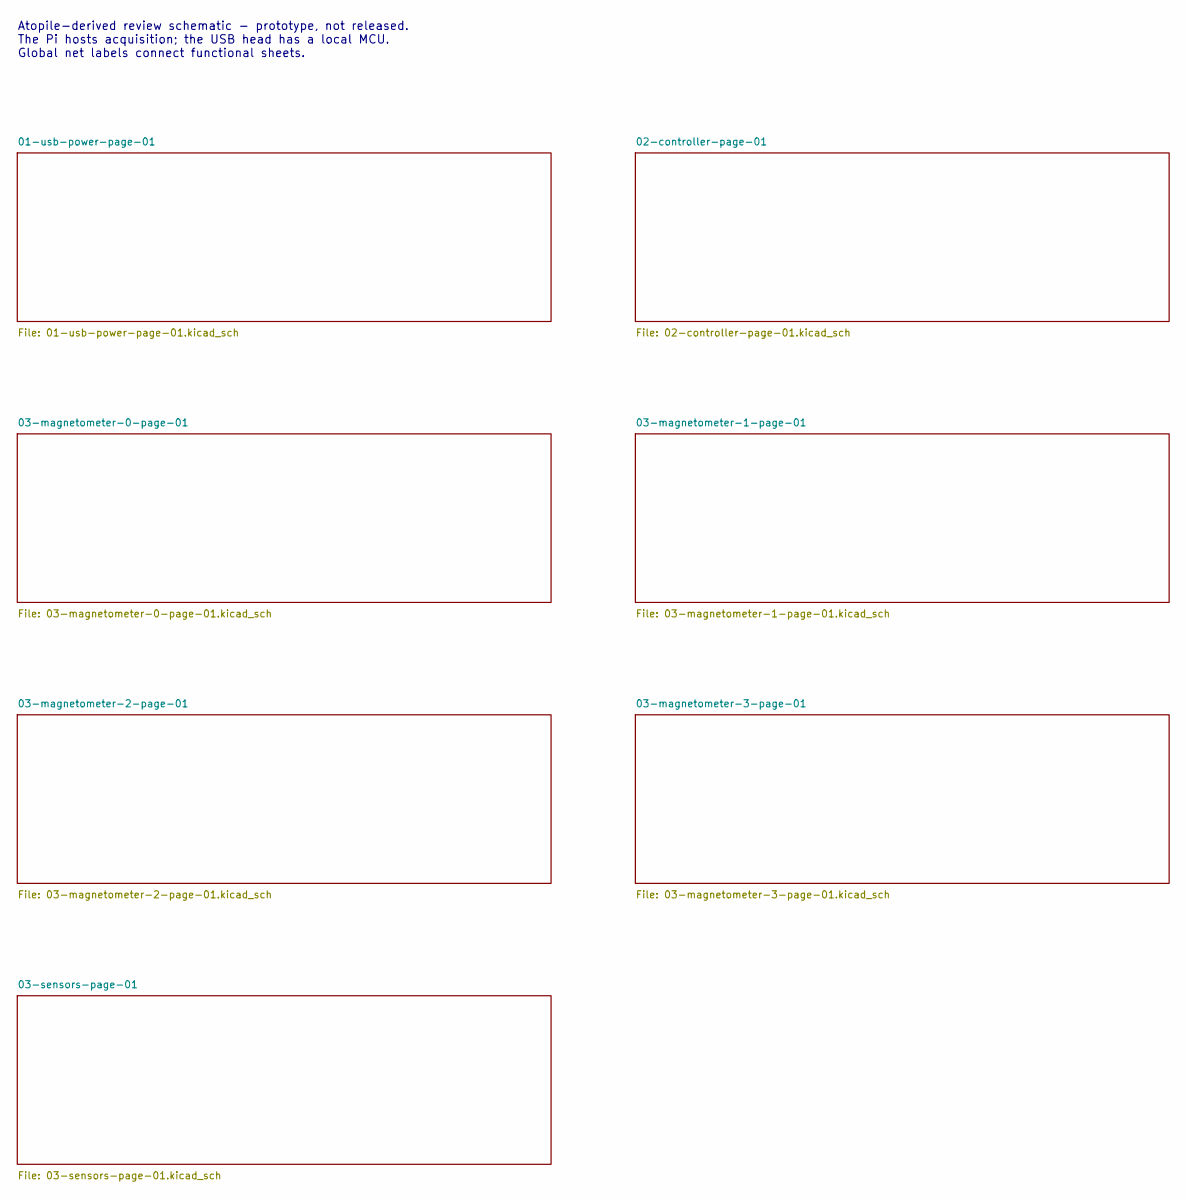
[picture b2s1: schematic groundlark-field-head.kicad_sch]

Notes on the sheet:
Atopile-derived review schematic - prototype, not released. The Pi hosts acquisition; the USB head has a local MCU. Global net labels connect functional sheets.
